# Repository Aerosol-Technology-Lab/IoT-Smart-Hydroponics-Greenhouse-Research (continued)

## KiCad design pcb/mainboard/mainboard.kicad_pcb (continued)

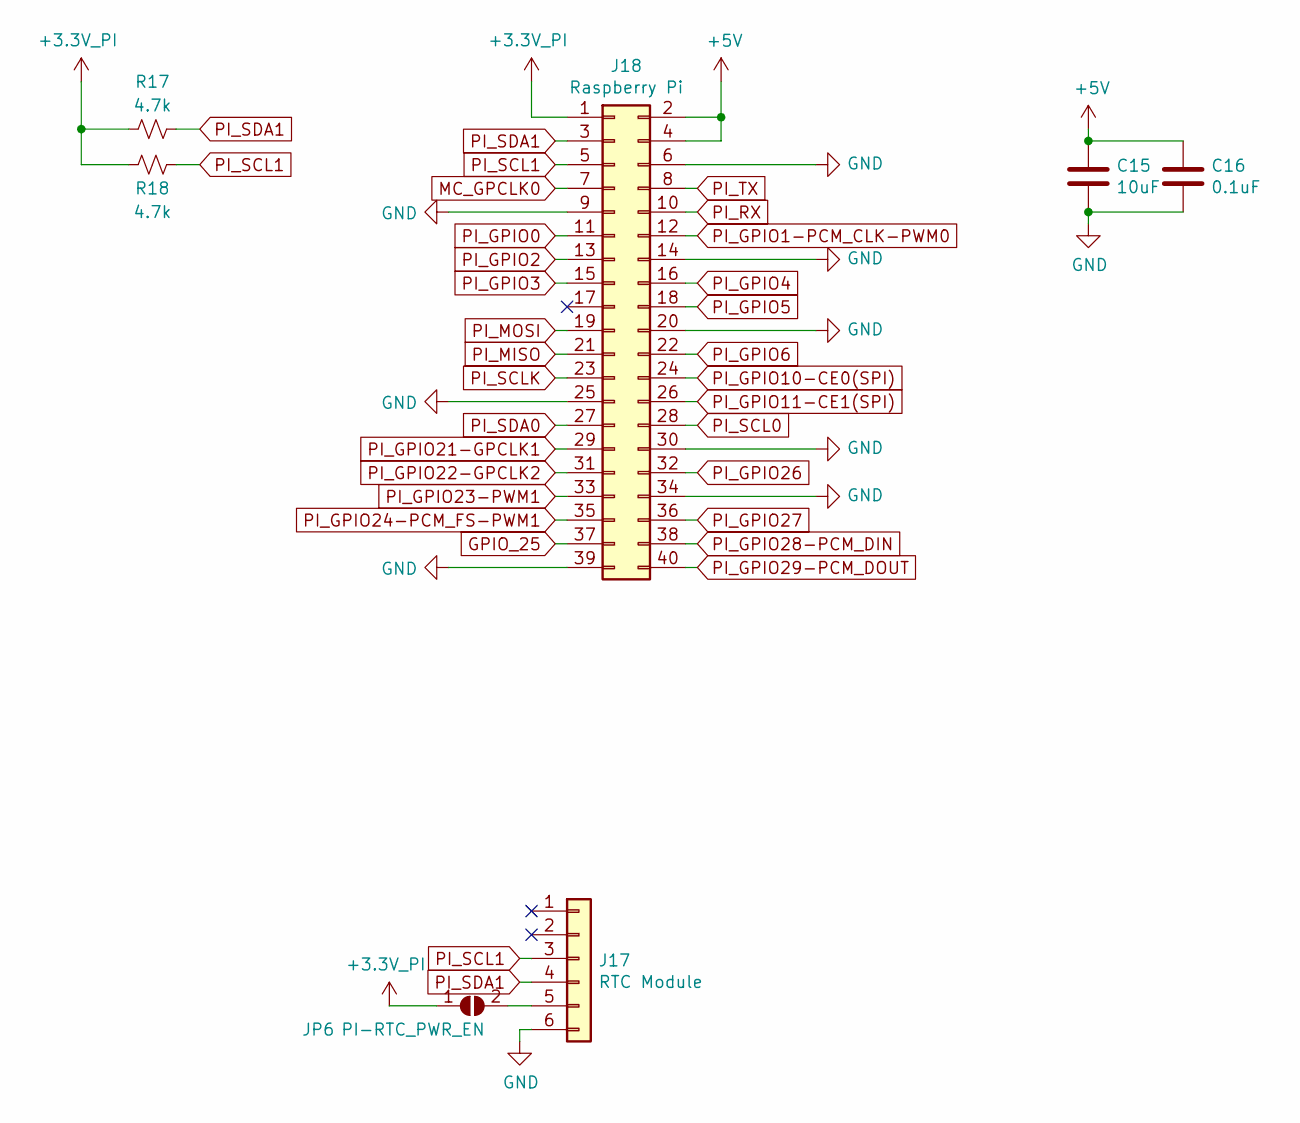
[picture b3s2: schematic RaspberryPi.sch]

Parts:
C15: 10uF; C_0603_1608Metric
C16: 0.1uF; C_0603_1608Metric
J17: RTC Module; PinSocket_1x06_P2.54mm_Vertical
J18: Raspberry Pi; IDC-Header_2x20_P2.54mm_Vertical
JP6: PI-RTC_PWR_EN; SolderJumper-2_P1.3mm_Open_TrianglePad1.0x1.5mm
R17, R18: 4.7k; R_0603_1608Metric

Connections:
+5V: C15.1, C16.1, J18.2, J18.4; also elsewhere on the board
GND: C15.2, C16.2, J17.6, J18.6, J18.9, J18.14, J18.20, J18.25, J18.30, J18.34, J18.39; also elsewhere on the board
GPIO_25: J18.37
MC_GPCLK0: J18.7
unnamed: J17.5, JP6.2 (B)
PI_GPIO0: J18.11; also elsewhere on the board
PI_GPIO1-PCM_CLK-PWM0: J18.12
PI_GPIO2: J18.13
PI_GPIO3: J18.15
PI_GPIO4: J18.16
PI_GPIO5: J18.18
PI_GPIO6: J18.22
PI_GPIO10-CE0(SPI): J18.24
PI_GPIO11-CE1(SPI): J18.26
PI_GPIO21-GPCLK1: J18.29
PI_GPIO22-GPCLK2: J18.31
PI_GPIO23-PWM1: J18.33
PI_GPIO24-PCM_FS-PWM1: J18.35
PI_GPIO26: J18.32
PI_GPIO27: J18.36
PI_GPIO28-PCM_DIN: J18.38
PI_GPIO29-PCM_DOUT: J18.40
PI_MISO: J18.21
PI_MOSI: J18.19
PI_RX: J18.10; also elsewhere on the board
PI_SCL0: J18.28
PI_SCL1: J17.3, J18.5, R18.1; also elsewhere on the board
PI_SCLK: J18.23
PI_SDA0: J18.27
PI_SDA1: J17.4, J18.3, R17.1; also elsewhere on the board
PI_TX: J18.8; also elsewhere on the board
~: J18.1, JP6.1 (A), R17.2, R18.2

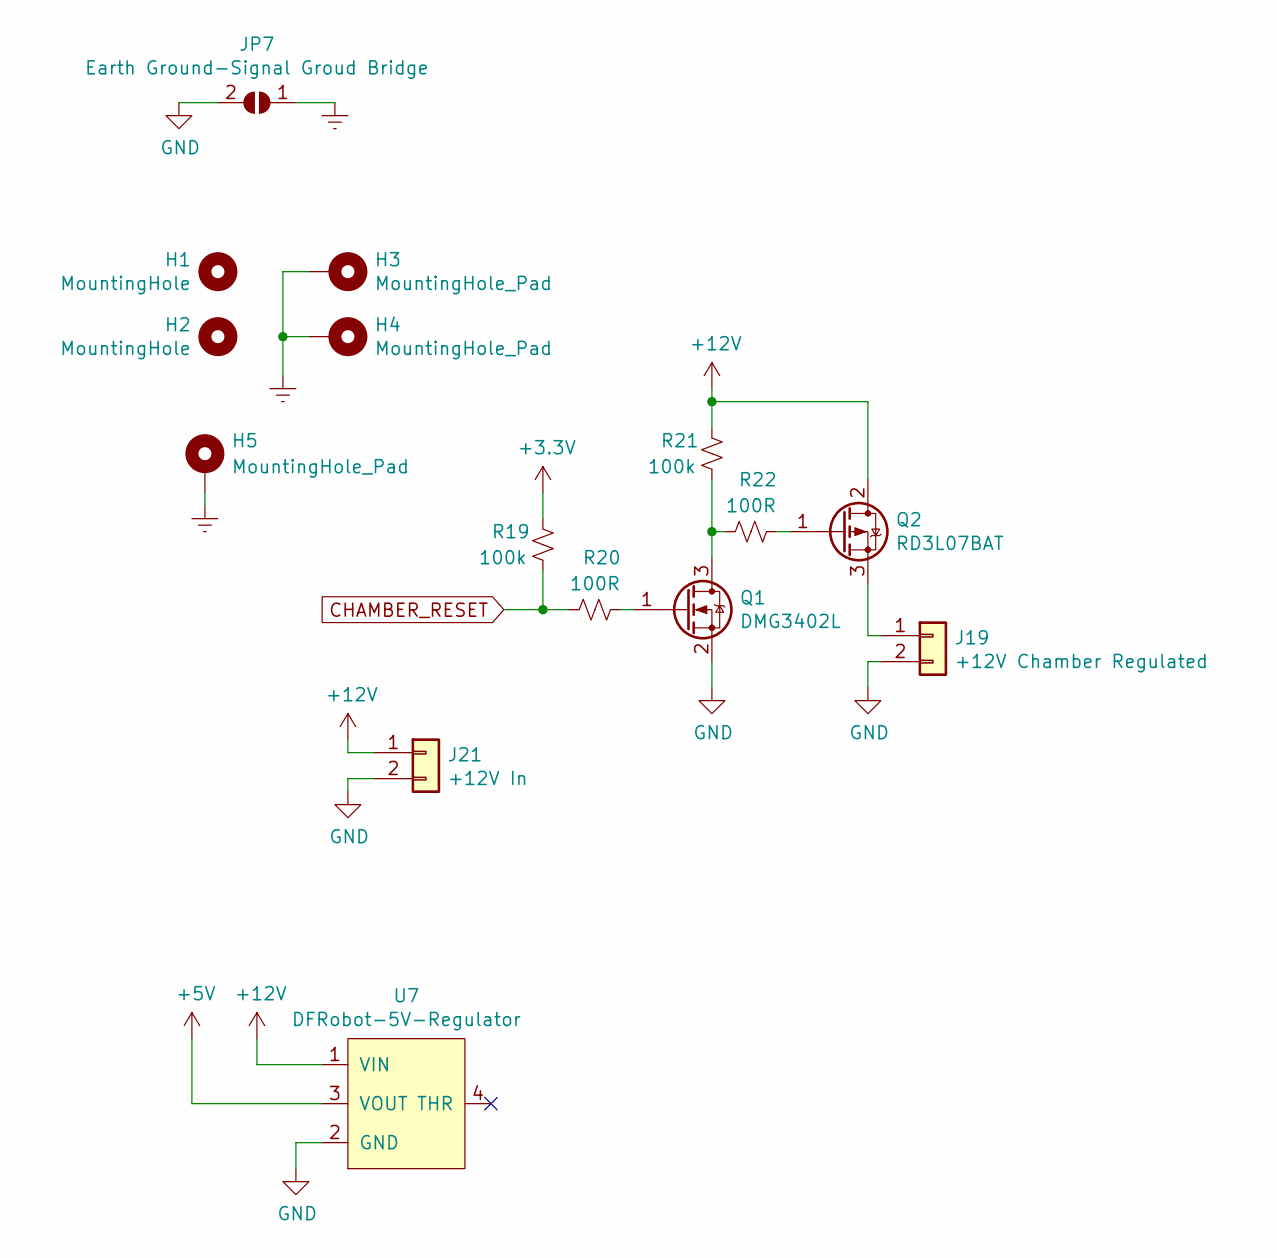
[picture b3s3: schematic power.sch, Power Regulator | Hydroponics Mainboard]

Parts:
H1, H2: MountingHole; MountingHole_3.2mm_M3_ISO7380_Pad_TopOnly
H3, H4, H5: MountingHole_Pad; MountingHole_3.2mm_M3_Pad_Via
J19: +12V Chamber Regulated; YK7010223000G(2POS-Terminal-Block)
J21: +12V In; YK7010223000G(2POS-Terminal-Block)
JP7: Earth Ground-Signal Groud Bridge; SolderJumper-2_P1.3mm_Open_TrianglePad1.0x1.5mm
Q1: DMG3402L; SOT-23
Q2: RD3L07BAT; TO-252-2
R19, R21: 100k; R_0603_1608Metric
R20, R22: 100R; R_0603_1608Metric
U7: DFRobot-5V-Regulator

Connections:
+3V3: R19.1; also elsewhere on the board
+5V: U7.3 (VOUT); also elsewhere on the board
+12V: J21.1, Q2.2 (D), R21.1, U7.1 (VIN)
CHAMBER_RESET: R19.2, R20.2
Earth: H3.1, H4.1, H5.1, JP7.1 (A); also elsewhere on the board
GND: J19.2, J21.2, JP7.2 (B), Q1.2 (S), U7.2 (GND); also elsewhere on the board
unnamed: J19.1, Q2.3 (S)
unnamed: Q1.1 (G), R20.1
unnamed: Q1.3 (D), R21.2, R22.2
unnamed: Q2.1 (G), R22.1

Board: 2 copper layers, 75 parts (0 on the bottom side), 42 nets, no tracks yet.

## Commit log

2021-01-09 Add files
2021-01-10 Add app files
2021-01-12 Stuff
2021-02-20 Change how config is loaded to app
2021-02-20 A lot of stuff
2021-02-20 A lot more
2021-02-20 Cursor appearance disabled when on raspberry pi
2021-02-20 App will generate new config if it does not exist
2021-02-21 Add scroll bar to navigation
2021-02-21 Add icon config
2021-02-21 Add USB detection in the notification bar
2021-02-21 Clean up code
2021-02-21 Clean up
2021-02-21 misc changes
2021-02-21 Add sqlite3 module
2021-02-21 New class to handle initialization of SQLite3
2021-02-21 Improve error handling on Arduino connection
2021-02-22 Pretty changes
2021-02-22 More pretty changes
2021-02-22 Add shortcut to enable or disable mouse cursor
2021-02-22 Add routing
2021-02-22 Fix for routing issue
2021-02-22 Create autoupdate script for Raspberry Pi, updating code and allow updating and start at boot time
2021-02-22 Add comment
2021-02-22 Temporary disable only instance subprocess
2021-02-22 Build script
2021-02-23 Styling and add temperature support
2021-02-23 Preparing for more sensors
2021-02-23 Improve installer
2021-02-23 Fix bug that stops React from rendering
2021-02-23 Add focus when a navigation button is pressed
2021-02-23 Change architecture detection for Raspberry Pi
2021-02-23 Add working settings
2021-02-23 Add settings scene and change color scheme
2021-02-23 Add settings this time and color scheme
2021-02-24 Add shortcut to shutdown app
2021-02-26 Update compile flags for different boards on build
2021-02-26 .vscode file
2021-03-01 Add command to poll all data from sensors
2021-03-01 Bug fix
2021-03-01 Implement changes to simulator
2021-03-01 Add build tasks
2021-03-01 A lot of things
2021-03-01 Add ALL tag when requesting an all reading from USB
2021-03-02 Add a way to add more temperature sensors when needed
2021-03-03 Add i2c mux helper header
2021-03-03 Refactor temperature functions to waterTemperature for clarity
2021-03-04 Implement bme280 sensors
2021-03-04 Add insertion of rows into database
2021-03-05 Fix bug when requesting bme sensor index higher than 0 will label the reading as sensor 0
2021-04-05 Add code
2021-04-05 Add TDS sample code from DFRobot
2021-04-05 Remove files
2021-04-05 Reading temperature sensors depends on constant instead of hard code
2021-04-05 Add water temprature sensor wrapper
2021-04-05 Integrated water temperatue sensor
2021-04-05 Finish TDS sensor
2021-04-06 Add useful global functions like move and quicksort
2021-04-06 Add move option in constructor arguments
2021-04-06 Improve TDS reading algorithm
2021-04-06 Add DFRobot pH library
2021-04-06 Modify DFRobot PH library to add Arduino DUE compatibility
2021-04-06 Modify DFRobot library to accomodate differences between Arduino Due and the Uno
2021-04-07 Move template for utils to separate header
2021-04-07 Add Buffer class
2021-04-07 Add PH class
2021-04-07 Modify water temperature default initialization action
2021-04-07 Implement TDS sensor and buffer
2021-05-07 Add BME to dbhandler creation
2021-05-07 Add wip global modal
2021-05-07 Add safe space for globals
2021-06-05 Changes to settings page
2021-06-05 Add hydropnics app start config
2021-06-05 Modify start script
2021-06-05 Python will instead run yarn app
2021-06-05 Update install with new method
2021-06-05 Remove old code
2021-06-15 Add JSON library
2021-06-15 Fix library issues
2021-06-15 Add additional sensor code
2021-06-15 Add acquire bme280 from json
2021-06-15 Add error handling
2021-06-15 Add reading ambient light sensor
2021-06-15 Add documentation and enabled reading water temperature at main
2021-06-16 Fix new system to send data to arduino
2021-06-16 Fix bug where calling ambient light sensor instead called the water temperature sensor
2021-06-18 Add serial monitor tester
2021-06-18 Add simulation compatibility for ESP32 and fixed issues with recognizing commands
2021-06-18 Move ending character to the end of each command request
2021-06-25 Add DueFreeRTOS submodule library
2021-08-10 Made it so only one instance of the app can run at the same time
2021-08-10 Add new installer and script manager
2021-08-11 New installed
2021-09-01 Everything so far
2021-09-02 Can talk to Arduino
2021-09-03 If running on Pi, then it will attempt to chmod ttyACM0
2021-09-03 add sqlite3 on elc-rebuild
2021-09-03 Add recording to db
2021-09-03 Fix project settings
2021-09-03 Mostly works
2021-09-09 Remove sqlite3 to remove errors in RaspPi and saving data to CSV instead. Revist saving mechanism
2021-09-10 Remove unused code
2021-09-10 Add export to flash drive
2021-09-10 Fix bug
2021-09-10 Add DB format
2021-09-11 Add checks for raspberry pi usb
2021-09-11 Reduced font size to increase readability for Raspberry Pi
2021-09-11 Fix overflow in chamber
2021-09-11 works
2021-09-13 Fix various bugs related to wrong use of I2C mux
2021-09-13 Add reset request to sensor board
2021-09-14 Add support for ccs811 (CO2 and TVOC) sensor
2021-09-14 Add functionality for turbidity sensor
2021-09-14 Remove deprecated PH sensor
2021-09-14 Remove call for deprecated PH sensor function in main
2021-09-15 Add PH functionality
2021-09-15 Fix refactor in cpp file
2021-09-15 Add comments
2021-09-15 Add EC class
2021-09-15 Bug fixes with wrong voltage conversion to the external sensors
2021-09-15 Add support for sensors wrapper for all external sensors
2021-09-16 Test component to display system info
2021-09-16 Ignore hydro.csv
2021-09-16 Add diskspace library
2021-09-16 Add function for rest of the behavior
2021-09-17 Add functionality to read from more peripheral devices
2021-09-17 Add potential option to rebuild whole project
2021-09-17 Update comments
2021-09-17 Update autostart
2021-09-24 developments
2021-10-02 Moved reset functionality to utils file
2021-10-02 Bug fixes and added several senso functionality
2021-10-02 Add routine for calibrating peripheral sensors
2022-01-27 Add pcb
2022-02-17 Update .gitignore to ignore AppImage binaries for Linux
2022-02-17 Add pcb files
2022-02-17 Fix issues after upgrading to new pcb
2022-02-17 Renamed old repository
2022-03-05 Separte I2C sensor initialization to separate callable functions
2022-03-05 Disable CCS811 sensor for testing purposes
2022-03-05 Enable CCS811 sensors
2022-03-05 Fix compile errors
2022-03-05 Refactor i2cmux to i2cmux_access_chamber -> makes more sense in the context of function purpose
2022-03-05 Replace CO2 and TVOC to lowercase for consistency
2022-03-05 Add README to Arduino codebase
2022-03-05 Add documentation to README
2022-03-05 Improve documenation for Arduino codebase
2022-03-05 Fix README
2022-03-05 Add documentation to Arduino codebase
2022-03-05 Fix README bug in Arduino codebase
2022-03-05 Add jshint extension support as developer library
2022-03-05 Update README for Raspberry Pi codebase
2022-03-05 Graphical improvements
2022-03-05 Remove unused lines
2022-03-05 Move main program into a separate function
2022-03-06 Add comments, system is already performing as is
2022-03-06 Add CO2 and TVOC to display on frontend
2022-03-06 Change the method for determining if the sensor reading is valid from the frontend to new method -> less prone to issues
2022-03-06 Misc changes - made code prettier
2022-03-06 Forgot to put this in the last commit
2022-03-06 Add docker files
2022-03-06 Move docker files to root of Raspberry Pi codebase - was accidnetally saved to the fonts directory
2022-03-07 Modify Dockerfile
